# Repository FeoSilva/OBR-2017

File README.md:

# OBR 2017 - Equipe Robonáticos
Robô autônomo (Paulo) participante da Olimpíada Brasileira de Robótica.
<br><br>

Competições:
- Etapa Regional (FEI I) - 11/08/2017 - 1° lugar com 490 pts na somatória
- Etapa Estadual (FEI) - 09/09/2017

Resultados da Etapa Regional:
http://www.sistemaolimpo.org/regionais/results.php?eventID=3

<b>Divisões</b>
- Mecânica (12 versões do robô feitas para etapa regional utilizando o SolidWorks)
- Eletrônica (3 versões da Placa Principal para etapa regional utilizando o Eagle)
- Programação (45 versões do código até o final - Código em C++)

<b>Componentes do robô:</b><br>
<a href="https://store.arduino.cc/usa/arduino-mega-2560-rev3">- 1x Arduino Mega</a><br>
<a href="https://www.pololu.com/product/3045">- 4x 298:1 Micro Metal Gearmotor HPCB 12V</a><br>
<a href="https://www.pololu.com/product/713/resources">- 1x TB6612FNG (Controlador dos Motores);</a><br>
<a href="https://www.pololu.com/product/1425">- 8x Rodas Pololu 70x8mm</a><br>
<a href="https://www.filipeflop.com/produto/acelerometro-e-giroscopio-3-eixos-6-dof-mpu-6050/">- 1x MPU6050 - Acelerômetro e Giroscópio</a><br>
<a href="https://www.pololu.com/product/1134">- 4x Sharp Sensor Digital 2-10 cm</a><br>
<a href="https://www.pololu.com/product/2464">- 2x Sharp Sensor Analógico 4-30 cm</a><br>
<a href="https://www.pololu.com/product/960">- 1x QTR Sensor Array Analógico</a><br>
<a href="http://www.usinainfo.com.br/sensores-para-arduino/sensor-de-cor-para-arduino-tcs230-2810.html">- 2x TSC 230 - Sensor de Cor</a><br>
<a href="http://produto.mercadolivre.com.br/MLB-876602966-bateria-lipo-turnigy-2200mah-3s-111v-20c-_JM">- 1x Bateria de Li-po 11.1V 3S</a><br>
<a href="https://www.filipeflop.com/produto/servo-towerpro-mg995-metalico/">- 1x Servo MG995 15 kg.F.cm</a><br>
<a href="https://www.filipeflop.com/produto/micro-servo-9g-sg90-towerpro/">- 1x Micro servo SG90 Tower Pro</a>

<b>Fatores que serão melhorados/implementados para Etapa Estadual</b>
- Inclusão de encoder nos motores para aperfeiçoar as verificações e curvas do robô<br>
- Replanejamento dos sensores de distância para identificar as vítimas<br>
- Aperfeiçoamento da mecânica geral do robô para melhorar o centro de massa e diminuir sua altura<br>
- Aperfeiçoamento do mecanismo de recolher as vitímas<br>
- Implementação do algoritmo de cálculo percentual de proximidade de cor para detectar melhor a fita verde

<b>Integrantes:</b>
- Felipe Oliveira Silva (18 anos - Programação / Eletrônica);
- Antonio Pereira de Lima Neto (18 anos - Programação);
- Giovanna Ferreira Diodato (16 anos - Programação);
- Felipe de Souza Tiozo (17 anos - Mecânica / Eletrônica);

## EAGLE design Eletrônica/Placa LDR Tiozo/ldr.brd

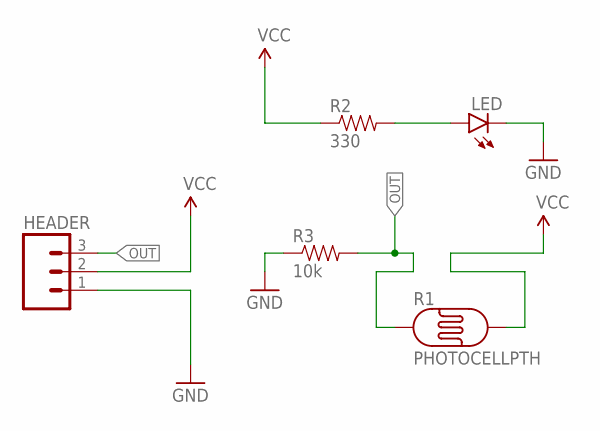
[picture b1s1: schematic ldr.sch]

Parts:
HEADER: M03PTH; 1X03
LED: LED5MM
R1: PHOTOCELLPTH; PHOTOCELL
R2: 330; AXIAL-0.3EZ
R3: 10k; AXIAL-0.3EZ

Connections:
GND: HEADER.1, LED.K (C), R3.P$1 (1)
unnamed: LED.A, R2.P$2 (2)
OUT: HEADER.3, R1.1, R3.P$2 (2)
VCC: HEADER.2, R1.2, R2.P$1 (1)

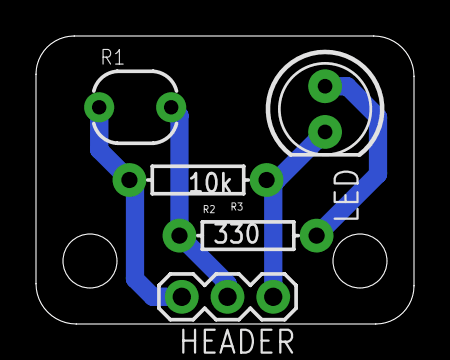
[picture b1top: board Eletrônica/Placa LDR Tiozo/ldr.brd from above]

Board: 2 copper layers, 21.0 x 16.0 mm, 5 parts (0 on the bottom side), 4 nets.

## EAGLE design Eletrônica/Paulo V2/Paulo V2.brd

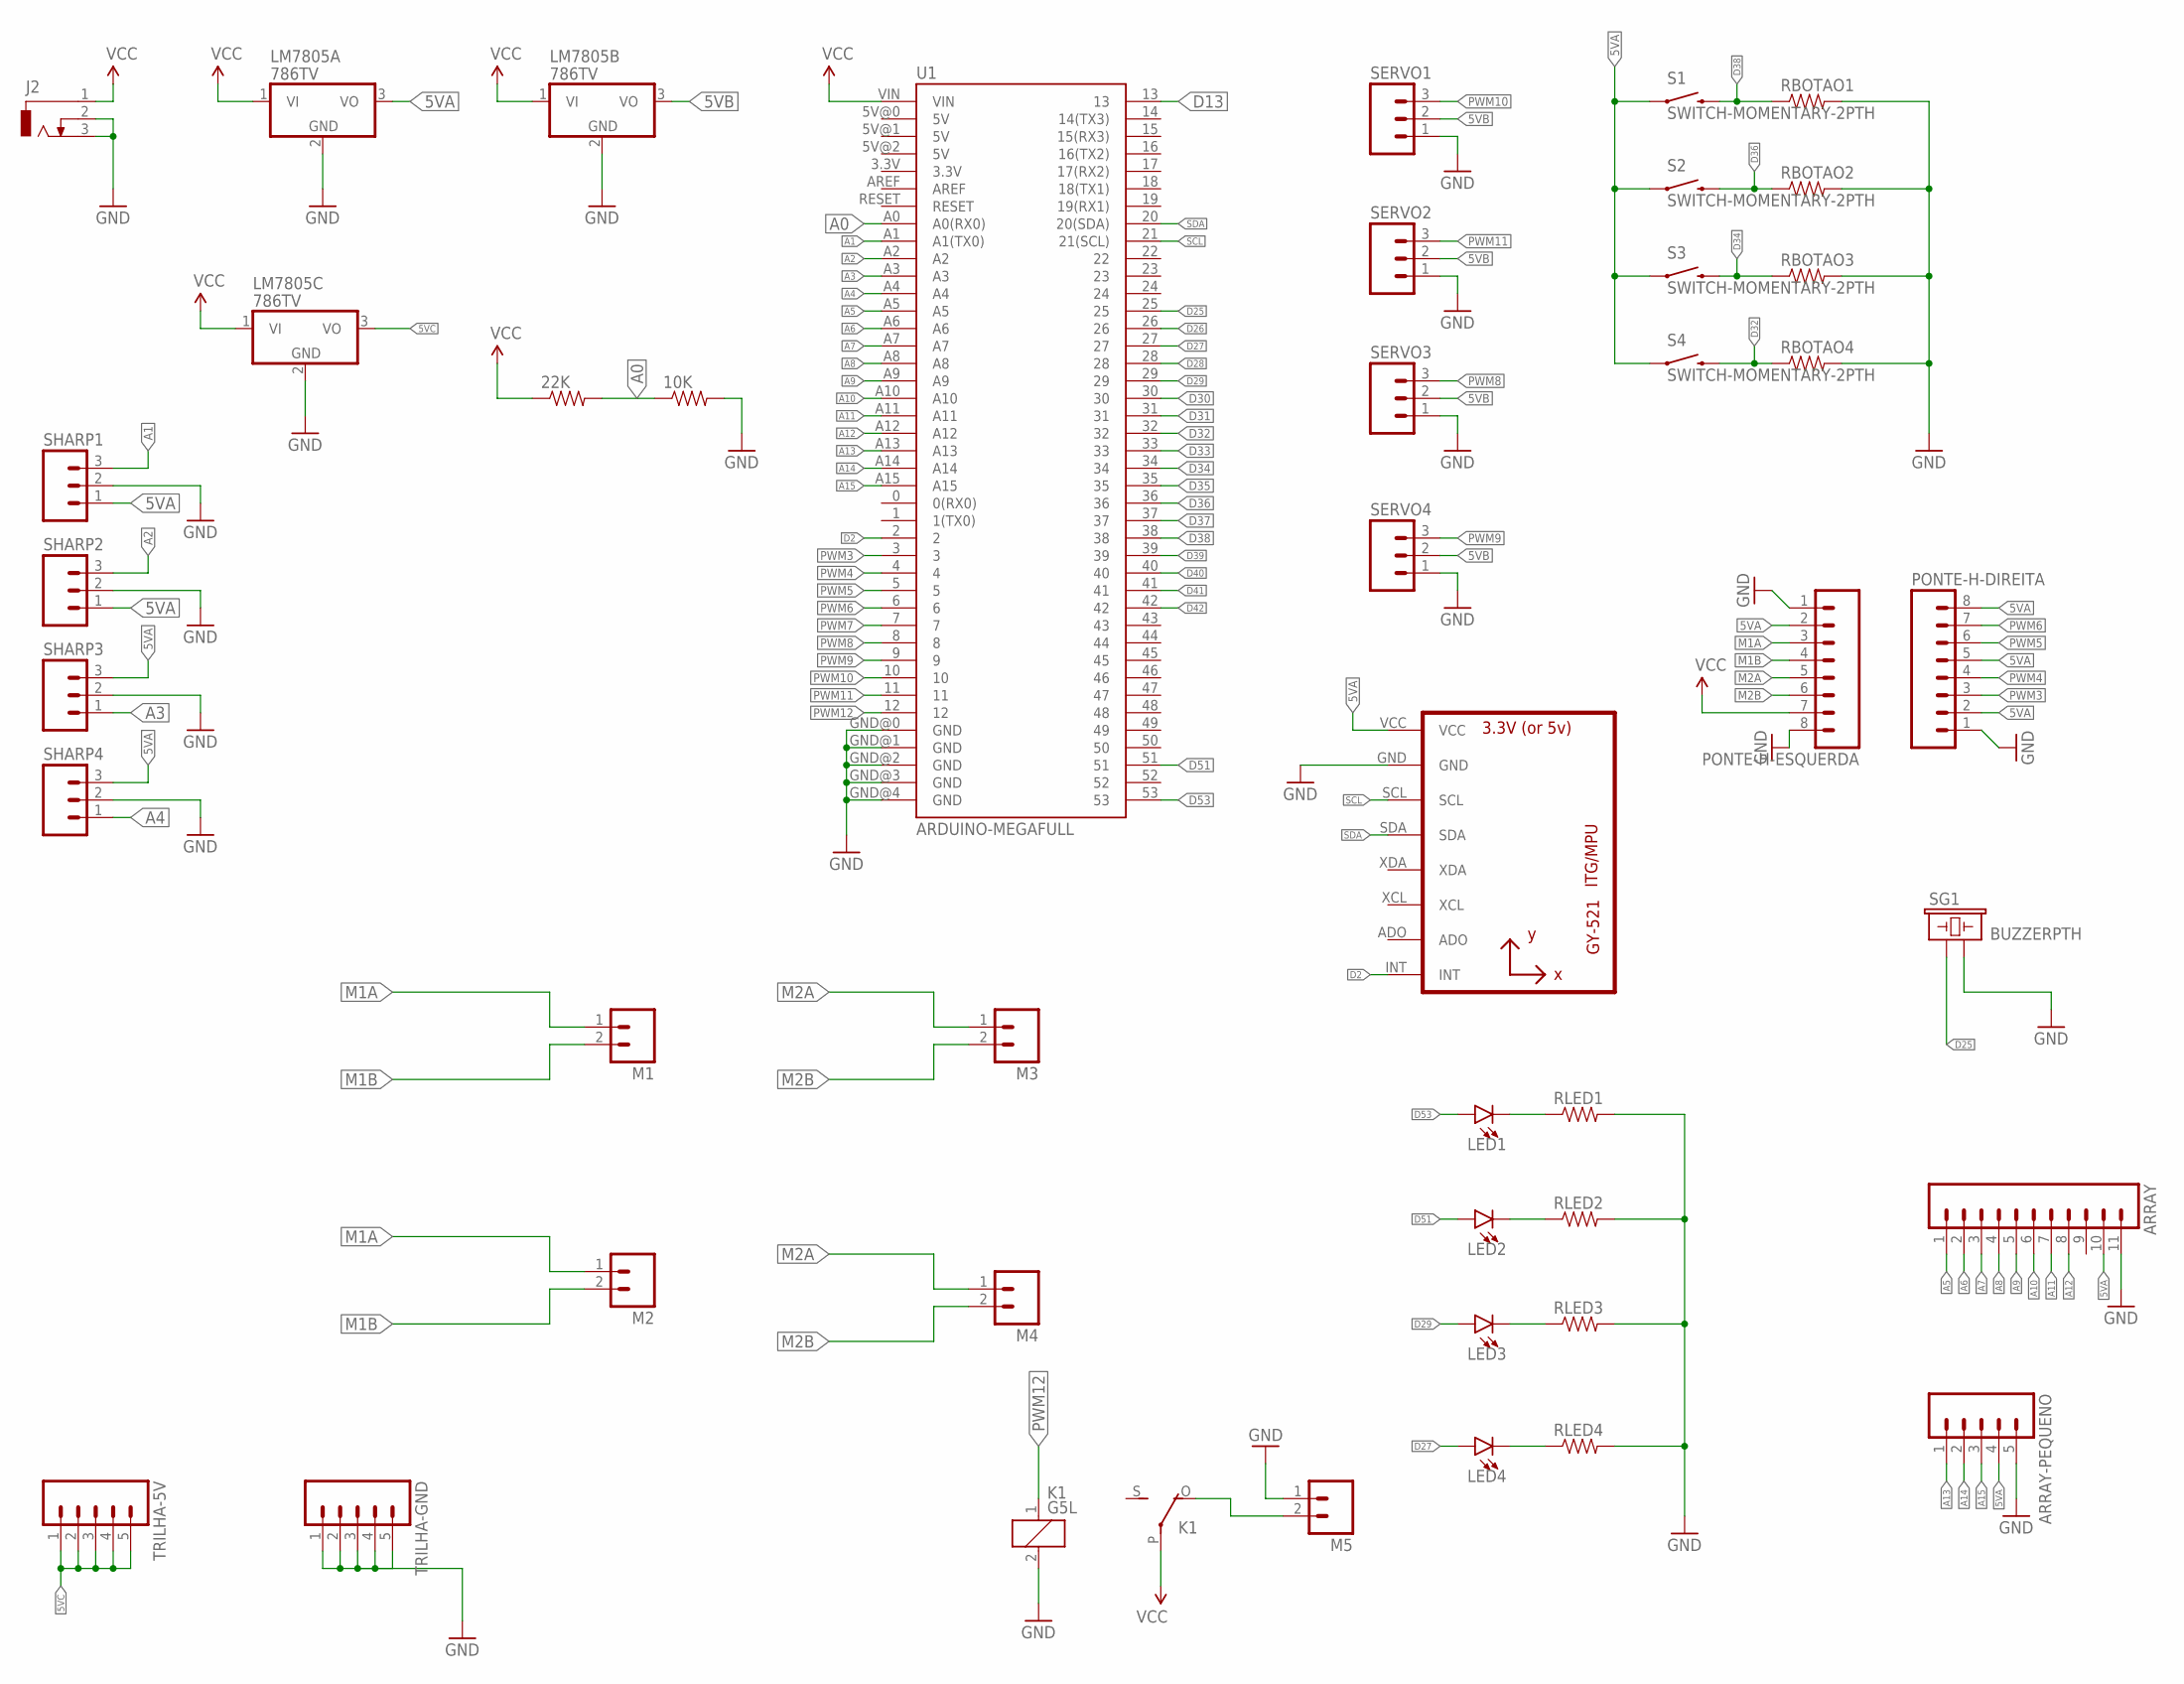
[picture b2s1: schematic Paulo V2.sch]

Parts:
10K, 22K: RESISTOREZ; AXIAL-0.3EZ
ARRAY: M11POGOPIN_HOLES_ONLY; 1X11_HOLES_ONLY
ARRAY-PEQUENO: M05PTH; 1X05
J2: DCJ0303
K1: G5L; G5LE
LED1, LED2, LED3, LED4: LED5MM; LED_5MM
LM7805A, LM7805B, LM7805C: 786TV; TO220V
M1, M2, M3, M4, M5: M02JST-PTH-VERT; JST-2-PTH-VERT
PONTE-H-DIREITA: M08NO_SILK; 1X08_PIN1_NO_SILK
PONTE-H-ESQUERDA: M08NO_SILK; 1X08_PIN1_NO_SILK
RBOTAO1, RBOTAO2, RBOTAO3, RBOTAO4: RESISTOREZ; AXIAL-0.3EZ
RLED1, RLED2, RLED3, RLED4: RESISTOREZ; AXIAL-0.3EZ
S1, S2, S3, S4: SWITCH-MOMENTARY-2PTH; TACTILE-PTH
SERVO1, SERVO2, SERVO3, SERVO4: M03LONGPADS; 1X03_LONGPADS@1
SG1: BUZZERPTH; BUZZER-12MM
SHARP1, SHARP2, SHARP3, SHARP4: M03LONGPADS; 1X03_LONGPADS@1
TRILHA-5V: M05PTH; 1X05
TRILHA-GND: M05PTH; 1X05
U1: ARDUINO-MEGAFULL; ARDUINO_MEGA
U2: GY-521MPU6050; GY-521

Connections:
5VA: ARRAY.10, ARRAY-PEQUENO.4, LM7805A.3 (VO), PONTE-H-DIREITA.2, PONTE-H-DIREITA.5, PONTE-H-DIREITA.8, PONTE-H-ESQUERDA.2, S1.1, S2.1, S3.1, S4.1, SHARP1.1, SHARP2.1, SHARP3.3, SHARP4.3, U2.VCC
5VB: LM7805B.3 (VO), SERVO1.2, SERVO2.2, SERVO3.2, SERVO4.2
5VC: LM7805C.3 (VO), TRILHA-5V.1, TRILHA-5V.2, TRILHA-5V.3, TRILHA-5V.4, TRILHA-5V.5
A0: 10K.P$1 (1), 22K.P$2 (2), U1.A0 (A0(RX0))
A1: SHARP1.3, U1.A1 (A1(TX0))
A2: SHARP2.3, U1.A2
A3: SHARP3.1, U1.A3
A4: SHARP4.1, U1.A4
A5: ARRAY.1, U1.A5
A6: ARRAY.2, U1.A6
A7: ARRAY.3, U1.A7
A8: ARRAY.4, U1.A8
A9: ARRAY.5, U1.A9
A10: ARRAY.6, U1.A10
A11: ARRAY.7, U1.A11
A12: ARRAY.8, U1.A12
A13: ARRAY-PEQUENO.1, U1.A13
A14: ARRAY-PEQUENO.2, U1.A14
A15: ARRAY-PEQUENO.3, U1.A15
D2: U1.2, U2.INT
D13: U1.13
D25: SG1.+ (1), U1.25
D26: U1.26
D27: LED4.A, U1.27
D28: U1.28
D29: LED3.A, U1.29
D30: U1.30
D31: U1.31
D32: RBOTAO4.P$1 (1), S4.3 (2), U1.32
D33: U1.33
D34: RBOTAO3.P$1 (1), S3.3 (2), U1.34
D35: U1.35
D36: RBOTAO2.P$1 (1), S2.3 (2), U1.36
D37: U1.37
D38: RBOTAO1.P$1 (1), S1.3 (2), U1.38
D39: U1.39
D40: U1.40
D41: U1.41
D42: U1.42
D51: LED2.A, U1.51
D53: LED1.A, U1.53
GND: 10K.P$2 (2), ARRAY.11, ARRAY-PEQUENO.5, J2.2, J2.3, K1.2, LM7805A.2 (GND), LM7805B.2 (GND), LM7805C.2 (GND), M5.1, PONTE-H-DIREITA.1, PONTE-H-ESQUERDA.1, PONTE-H-ESQUERDA.8, RBOTAO1.P$2 (2), RBOTAO2.P$2 (2), RBOTAO3.P$2 (2), RBOTAO4.P$2 (2), RLED1.P$2 (2), RLED2.P$2 (2), RLED3.P$2 (2), RLED4.P$2 (2), SERVO1.1, SERVO2.1, SERVO3.1, SERVO4.1, SG1.- (2), SHARP1.2, SHARP2.2, SHARP3.2, SHARP4.2, TRILHA-GND.1, TRILHA-GND.2, TRILHA-GND.3, TRILHA-GND.4, TRILHA-GND.5, U1.GND@0 (GND), U1.GND@1 (GND), U1.GND@2 (GND), U1.GND@3 (GND), U1.GND@4 (GND), U2.GND
M1A: M1.1, M2.1, PONTE-H-ESQUERDA.3
M1B: M1.2, M2.2, PONTE-H-ESQUERDA.4
M2A: M3.1, M4.1, PONTE-H-ESQUERDA.5
M2B: M3.2, M4.2, PONTE-H-ESQUERDA.6
unnamed: LED1.K (C), RLED1.P$1 (1)
unnamed: LED2.K (C), RLED2.P$1 (1)
unnamed: LED3.K (C), RLED3.P$1 (1)
unnamed: LED4.K (C), RLED4.P$1 (1)
unnamed: K1.O, M5.2
PWM3: PONTE-H-DIREITA.3, U1.3
PWM4: PONTE-H-DIREITA.4, U1.4
PWM5: PONTE-H-DIREITA.6, U1.5
PWM6: PONTE-H-DIREITA.7, U1.6
PWM7: U1.7
PWM8: SERVO3.3, U1.8
PWM9: SERVO4.3, U1.9
PWM10: SERVO1.3, U1.10
PWM11: SERVO2.3, U1.11
PWM12: K1.1, U1.12
SCL: U1.21 (21(SCL)), U2.SCL
SDA: U1.20 (20(SDA)), U2.SDA
VCC: 22K.P$1 (1), J2.1, K1.P, LM7805A.1 (VI), LM7805B.1 (VI), LM7805C.1 (VI), PONTE-H-ESQUERDA.7, U1.VIN

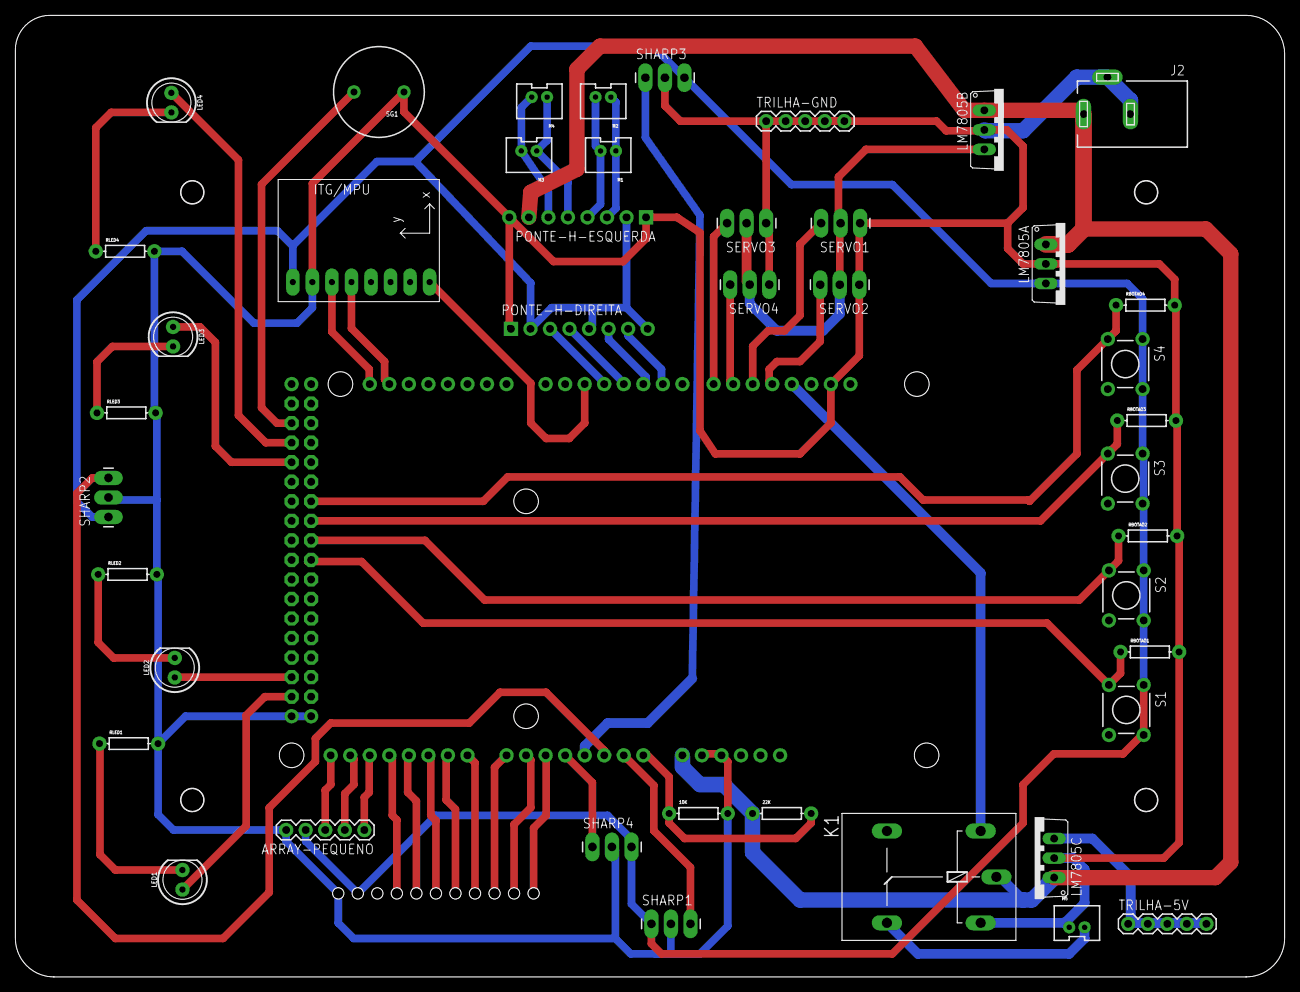
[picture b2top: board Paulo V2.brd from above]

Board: 2 copper layers, 165.0 x 125.0 mm, 45 parts (1 on the bottom side), 51 nets.

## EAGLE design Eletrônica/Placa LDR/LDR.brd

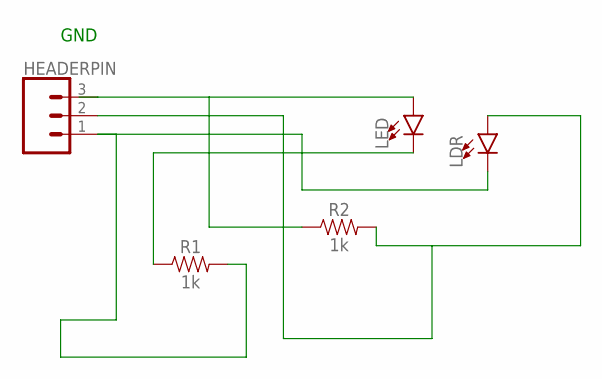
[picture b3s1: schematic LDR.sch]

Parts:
HEADERPIN: CONN_03; 1X03
LDR: LED5MM; LED_5MM
LED: LED5MM; LED_5MM
R1, R2: 1k; AXIAL-0.3

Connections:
unnamed: HEADERPIN.3, LED.A, R2.P$1 (1)
unnamed: LED.K (C), R1.P$1 (1)
unnamed: HEADERPIN.1, LDR.K (C), R1.P$2 (2)
unnamed: HEADERPIN.2, LDR.A, R2.P$2 (2)

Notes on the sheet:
GND

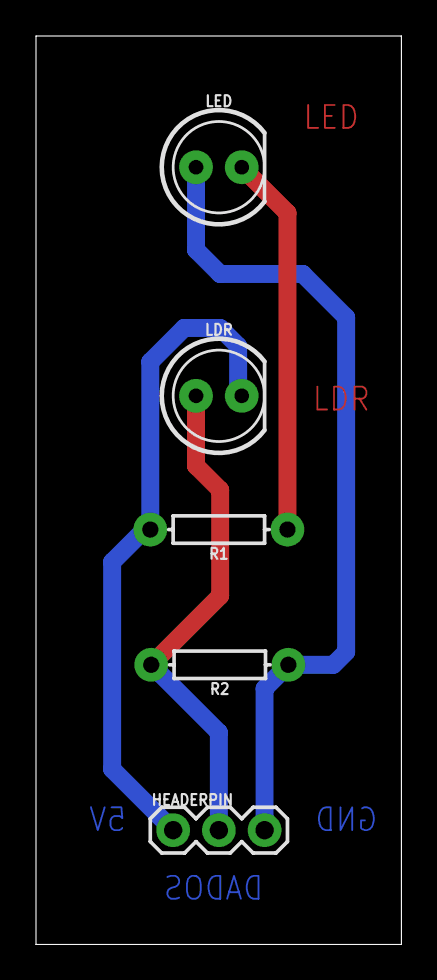
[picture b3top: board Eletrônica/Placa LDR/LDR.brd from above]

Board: 2 copper layers, 20.3 x 50.5 mm, 5 parts (0 on the bottom side), 4 nets.

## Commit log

2017-08-13 Add photos
2017-08-14 Create LICENSE
2017-08-14 Initial Commit to State Competition
2017-08-30 Limpeza da Programação e Leitura de Sensores
2017-08-31 Teste PID e retirada do RGB
2017-09-01 Reading Sharps, Exclude Digital Sharps of Regional
2017-09-01 Methods and functions of the green
2017-09-04 Exclude function read green sensors and move to read all sensors
2017-09-04 Quadrature encoder robot move
2017-09-04 Organization and annotation of all methods and functions
2017-09-07 Implements MPU6050 with bugs
2017-09-07 Fix bug in MPU6050 curves
2017-09-07 Fix final changes mpu 6050
2017-09-07 Fix encoder debug duplicated
2017-09-07 Fix bugs in MPU6050
2017-09-07 Change the values of follow line
2017-09-08 Development of the rescue
2017-09-08 Change port sensors
2017-09-08 Fix follow line bugs
2017-09-08 Fix ramp changes
2017-09-08 Servo default position
2017-09-09 Finish rescue
2017-09-09 Initial commit of obstacle task

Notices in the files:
parts and their libraries:
SparkFun-Aesthetics: Licensing: Creative Commons ShareAlike 4.0 International - https://creativecommons.org/licenses/by-sa/4.0
